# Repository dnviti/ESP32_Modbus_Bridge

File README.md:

# **Dual ESP32 Modbus TCP to Wi-Fi Bridge**

This repository contains the KiCad project files and design documentation for a custom PCB that acts as an industrial data bridge. The board reads data from a PLC via Modbus TCP over Ethernet and transmits it to a web server via Wi-Fi.

## **High-Level Functionality**

The board is designed around a dual-ESP32 architecture to handle network tasks concurrently and without interference:

* **ESP32 \#1 (Modbus Master):**  
  * Connects to an industrial network via a hardwired Ethernet (RJ45) port.  
  * Communicates with a PLC using the Modbus TCP protocol to read register values.  
  * Transfers the retrieved data internally to the second ESP32.  
* **ESP32 \#2 (Web Client):**  
  * Receives data from the first ESP32 via a high-speed UART link.  
  * Connects to a local Wi-Fi network.  
  * Formats and sends the data to a specified web server endpoint using HTTPS POST requests.  
  * Drives a small I2C OLED display for real-time status monitoring (e.g., IP address, connection status, last sync time).

## **Key Hardware Features**

* **Dual ESP32-WROOM-32D Sockets:** For parallel processing of networking tasks.  
* **Robust Power Supply:** On-board 24V to 3.3V DC-DC buck converter to draw power directly from a PLC or industrial power rail.  
* **Wired & Wireless Connectivity:** Features a Hanrun HR911105A RJ45 port for Ethernet and integrated Wi-Fi/Bluetooth on the ESP32s.  
* **On-Board Debugging:** Includes FTDI programming headers, manual boot/reset buttons, and debug jumpers with status LEDs for each ESP32.  
* **I/O & Expansion:** Provides breakout headers for unused GPIO pins for future expansion and an I2C header for the status display.  
* **High-Density Design:** Utilizes 0402 package size for passive components to maintain a small form factor.

## **Full Documentation**

This README provides a brief overview. For complete technical details, including the full schematic specification, component list, bill of materials (BOM), and PCB layout guidelines, please refer to the comprehensive design document:

➡️ View the Complete Design & Manufacturing Specification  
(Note: Replace the link above with the actual URL to your hosted specification document.)

## **Project Files**

* **/Hardware**: Contains the KiCad project files (.pro, .sch, .kicad\_pcb).  
* **/Documentation**: Contains the full design specification PDF and other supporting documents.  
* **/Firmware**: Contains example Arduino/ESP-IDF source code for both ESP32 modules.  
* **/Gerbers**: Contains the final manufacturing files for PCB fabrication.

*This project is designed for industrial applications where reliability and clear diagnostics are critical. Please review the full documentation before fabrication or assembly.*

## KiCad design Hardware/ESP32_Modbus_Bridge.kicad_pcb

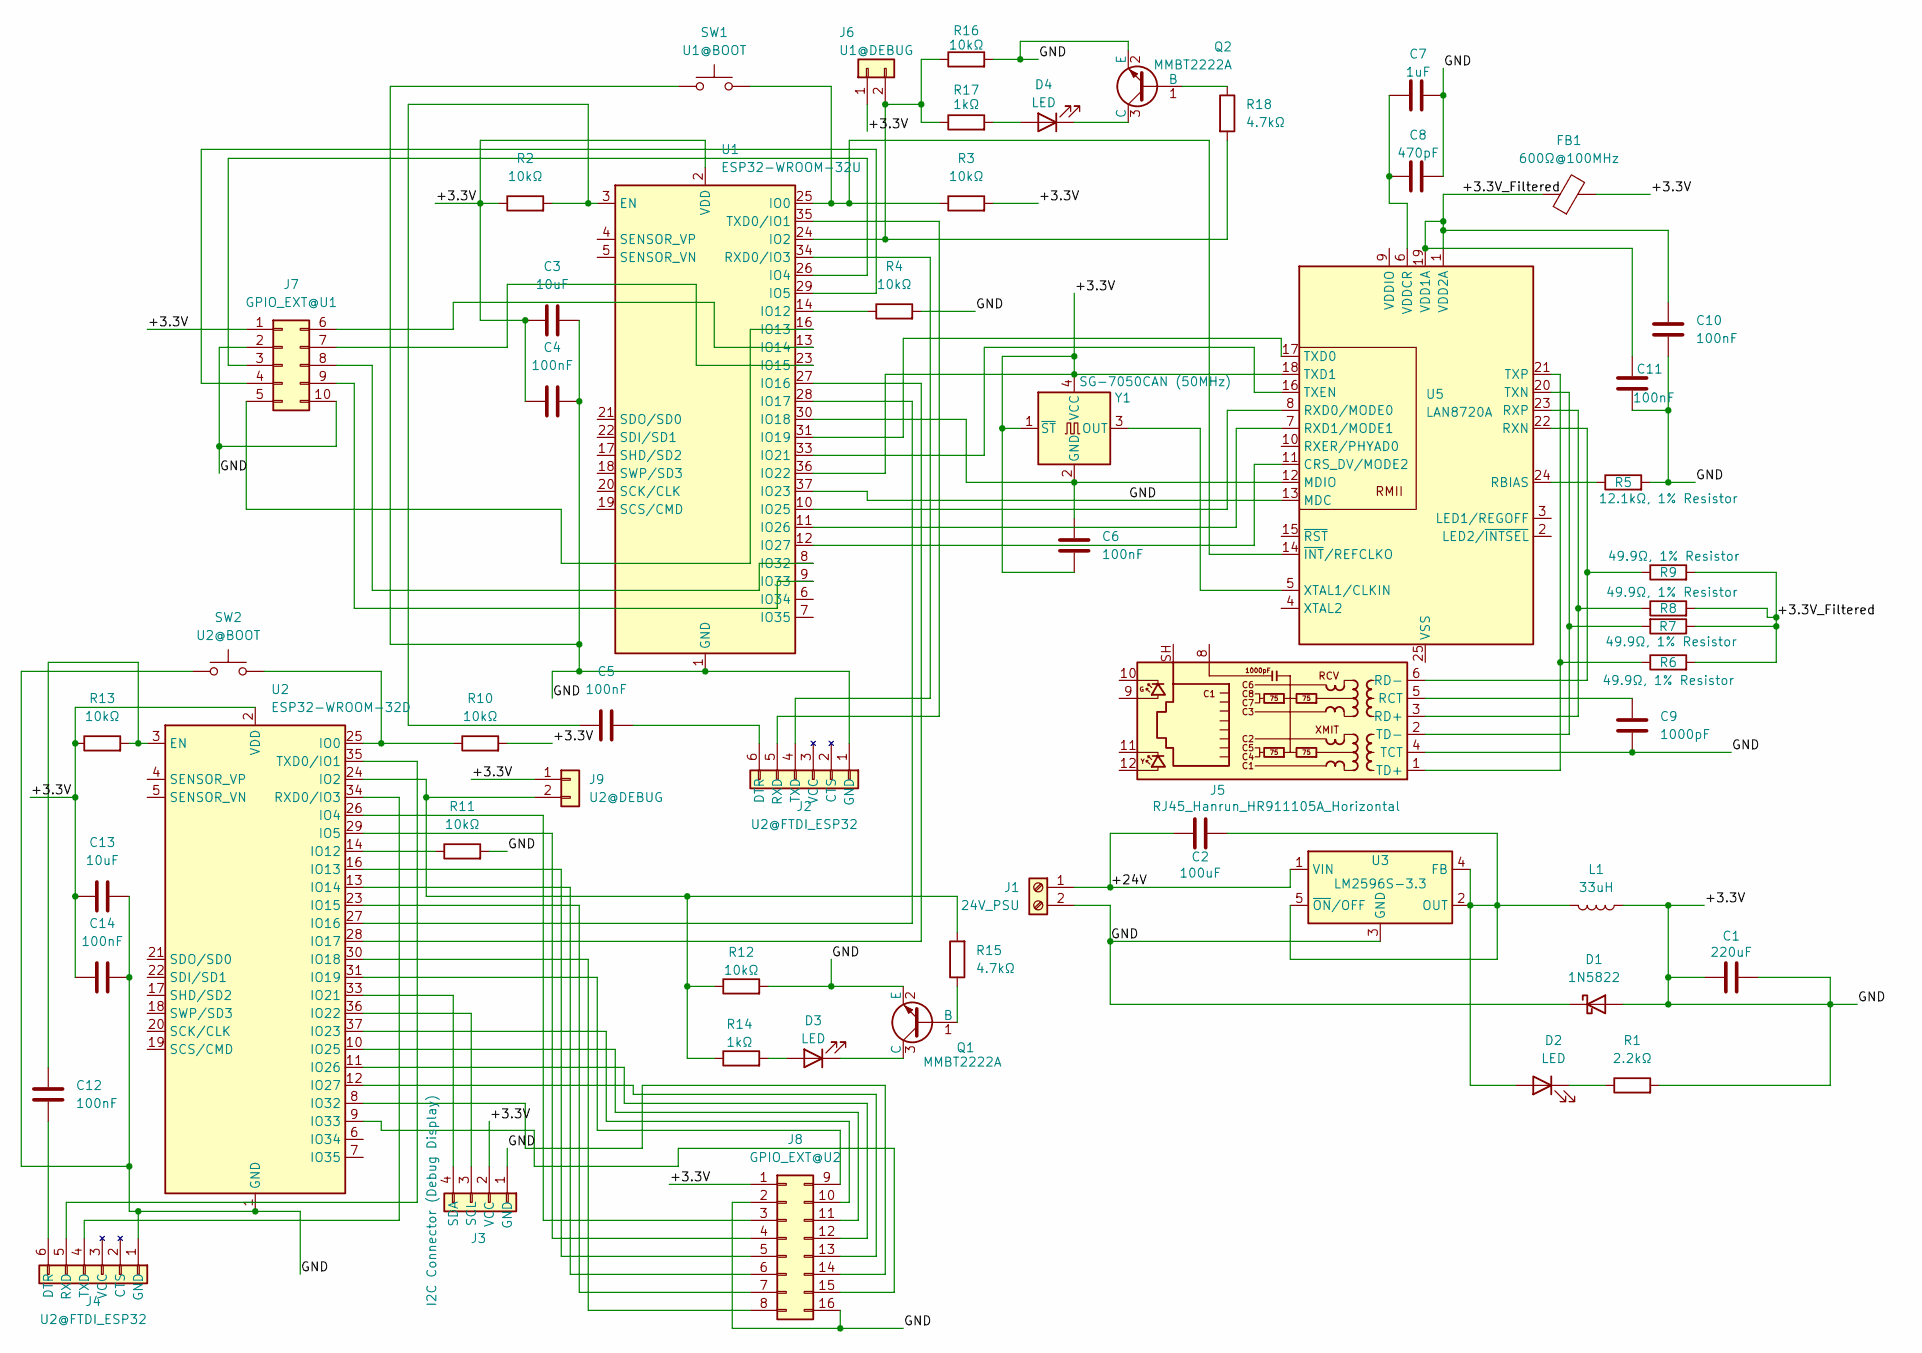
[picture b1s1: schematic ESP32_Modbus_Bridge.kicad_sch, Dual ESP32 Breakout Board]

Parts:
C1: 220uF; CP_Elec_8x10.5
C2: 100uF; CP_Elec_6.3x5.4
C3, C13: 10uF; C_0805_2012Metric
C4, C5, C6, C10, C11, C12, C14: 100nF; C_0402_1005Metric
C7: 1uF; C_01005_0402Metric
C8: 470pF; C_01005_0402Metric
C9: 1000pF; C_0805_2012Metric
D1: 1N5822; D_SMA
D2: LED; LED_0603_1608Metric
D3, D4: LED; LED_0402_1005Metric
FB1: 600Ω@100MHz; L_0603_1608Metric
J1: 24V_PSU; TerminalBlock_bornier-2_P5.08mm
J2, J4: U2@FTDI_ESP32; PinHeader_1x06_P2.54mm_Vertical
J3: I2C Connector (Debug Display); PinHeader_1x04_P2.54mm_Vertical
J5: RJ45_Hanrun_HR911105A_Horizontal
J6: U1@DEBUG; PinHeader_1x02_P2.54mm_Vertical
J7: GPIO_EXT@U1; PinHeader_2x05_P2.54mm_Vertical
J8: GPIO_EXT@U2; PinHeader_2x08_P2.54mm_Vertical
J9: U2@DEBUG; PinHeader_1x02_P2.54mm_Vertical
L1: 33uH; L_Bourns_SRR1260
Q1, Q2: MMBT2222A; SOT-23
R1: 2.2kΩ; R_0603_1608Metric
R2, R3, R4, R10, R11, R12, R13, R16: 10kΩ; R_0402_1005Metric
R5: 12.1kΩ, 1% Resistor; R_0402_1005Metric
R6, R7, R8, R9: 49.9Ω, 1% Resistor; R_0402_1005Metric
R14, R17: 1kΩ; R_0402_1005Metric
R15, R18: 4.7kΩ; R_0402_1005Metric
SW1: U1@BOOT; SW_SPST_PTS645
SW2: U2@BOOT; SW_SPST_PTS645
U1: ESP32-WROOM-32U
U2: ESP32-WROOM-32D
U3: LM2596S-3.3; TO-263-5_TabPin3
U5: LAN8720A; VQFN-24-1EP_4x4mm_P0.5mm_EP2.5x2.5mm_ThermalVias
Y1: SG-7050CAN (50MHz); Oscillator_SMD_SeikoEpson_SG8002CA-4Pin_7.0x5.0mm

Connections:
/+3.3V: C1.1, C1.2, C3.1, C3.2, C4.1, C4.2, C6.1, C7.2, C8.2, C9.1, C10.2, C11.2, C13.1, C13.2, C14.1, C14.2, D1.1 (K), D1.2 (A), FB1.2, J1.2, J2.1 (GND), J3.1 (GND), J3.2 (VCC), J4.1 (GND), J5.4 (TCT), J6.1, J7.1 (+3.3V), J7.2 (GND), J7.10 (GND), J8.1 (+3.3V), J8.2 (GND), J8.16 (GND), J9.1, L1.1, Q1.2 (E), Q2.2 (E), R1.2, R2.1, R3.2, R4.2, R5.2, R10.2, R11.2, R12.2, R13.1, R16.2, SW1.1, SW2.1, U1.1 (GND), U1.2 (VDD), U1.15 (GND), U1.36 (IO22), U1.37 (IO23), U1.38 (GND), U1.39 (GND), U2.1 (GND), U2.2 (VDD), U2.15 (GND), U2.38 (GND), U2.39 (GND), U3.3 (GND), U5.13 (MDC), U5.18 (TXD1), Y1.1 (~ST), Y1.4 (VCC)
/+3.3V_Filtered: C10.1, C11.1, FB1.1, R6.2, R7.1, R8.2, R9.2, U5.1 (VDD2A), U5.19 (VDD1A)
/+24V: C2.1, J1.1, U3.1 (VIN)
unnamed: C2.2, D2.2 (A), L1.2, U3.2 (OUT), U3.4 (FB), U3.5 (~ON/OFF)
unnamed: D2.1 (K), R1.1
unnamed: D3.2 (A), R14.2
unnamed: D3.1 (K), Q1.3 (C)
unnamed: D4.2 (A), R17.2
unnamed: D4.1 (K), Q2.3 (C)
unnamed: C5.2, J2.6 (DTR)
unnamed: J2.5 (RXD), U1.35 (TXD0/IO1)
unnamed: J2.4 (TXD), U1.34 (RXD0/IO3)
unnamed: J3.3 (SCL), U2.36 (IO22)
unnamed: J3.4 (SDA), U2.33 (IO21)
unnamed: C12.1, J4.6 (DTR)
unnamed: J4.5 (RXD), U2.35 (TXD0/IO1)
unnamed: J4.4 (TXD), U2.34 (RXD0/IO3)
unnamed: C9.2, J5.5 (RCT)
unnamed: J5.3 (RD+), R8.1, U5.23 (RXP)
unnamed: J5.6 (RD-), R9.1, U5.22 (RXN)
unnamed: J5.1 (TD+), R6.1, U5.21 (TXP)
unnamed: J5.2 (TD-), R7.2, U5.20 (TXN)
unnamed: J6.2, R16.1, R17.1, R18.2, U1.24 (IO2)
unnamed: J7.3 (GPIO4), U1.26 (IO4)
unnamed: J7.4 (GPIO5), U1.29 (IO5)
unnamed: J7.5 (GPIO13), U1.16 (IO13)
unnamed: J7.6 (GPIO14), U1.13 (IO14)
unnamed: J7.7 (GPIO15), U1.23 (IO15)
unnamed: J7.8 (GPIO32), U1.8 (IO32)
unnamed: J7.9 (GPIO33), U1.9 (IO33)
unnamed: J8.3 (P4), U2.26 (IO4)
unnamed: J8.4 (P5), U2.29 (IO5)
unnamed: J8.5 (P13), U2.16 (IO13)
unnamed: J8.6 (P14), U2.13 (IO14)
unnamed: J8.7 (P15), U2.23 (IO15)
unnamed: J8.8 (P18), U2.30 (IO18)
unnamed: J8.9 (P19), U2.31 (IO19)
unnamed: J8.10 (P23), U2.37 (IO23)
unnamed: J8.11 (P25), U2.10 (IO25)
unnamed: J8.12 (P26), U2.11 (IO26)
unnamed: J8.13 (P27), U2.12 (IO27)
unnamed: J8.14 (P32), U2.8 (IO32)
unnamed: J8.15 (P33), U2.9 (IO33)
unnamed: J9.2, R12.1, R14.1, R15.2, U2.24 (IO2)
unnamed: Q1.1 (B), R15.1
unnamed: Q2.1 (B), R18.1
unnamed: C5.1, R2.2, U1.3 (EN)
unnamed: R3.1, SW1.2, U1.25 (IO0), U5.14 (~INT/REFCLKO)
unnamed: R4.1, U1.14 (IO12)
unnamed: U1.27 (IO16), U2.28 (IO17)
unnamed: U1.28 (IO17), U2.27 (IO16)
unnamed: C6.2, U1.30 (IO18), U5.12 (MDIO), Y1.2 (GND)
unnamed: U1.31 (IO19), U5.17 (TXD0)
unnamed: U1.33 (IO21), U5.16 (TXEN)
unnamed: U1.10 (IO25), U5.8 (RXD0/MODE0)
unnamed: U1.11 (IO26), U5.7 (RXD1/MODE1)
unnamed: U1.12 (IO27), U5.11 (CRS_DV/MODE2)
unnamed: C12.2, R13.2, U2.3 (EN)
unnamed: R10.1, SW2.2, U2.25 (IO0)
unnamed: R11.1, U2.14 (IO12)
unnamed: R5.1, U5.24 (RBIAS)
unnamed: C7.1, C8.1, U5.6 (VDDCR)
unnamed: U5.5 (XTAL1/CLKIN), Y1.3 (OUT)

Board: 4 copper layers, 56 parts (0 on the bottom side), 63 nets, no tracks yet.

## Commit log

2025-06-12 v0.1 for schematics, no firmware
